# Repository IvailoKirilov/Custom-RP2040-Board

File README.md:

# Custom-RP2040-Board
This board is a simple RP2040 based MCU. The PCB was made with the help of the guide from Hack Club Stasis. 

I decided to make this board because I had wanted to make my own MCU for a while and when I saw the guide I instantly knew I had to make it. I learned quite a bit while making this project and now I will be bale to use this board for other projects.

This board has taken me about 7-8 hours to fully make. Below I have put some images of the finished board.

Schematic:

PCB (front):

PCB (back):

3D View (top):

3D View (bottom):

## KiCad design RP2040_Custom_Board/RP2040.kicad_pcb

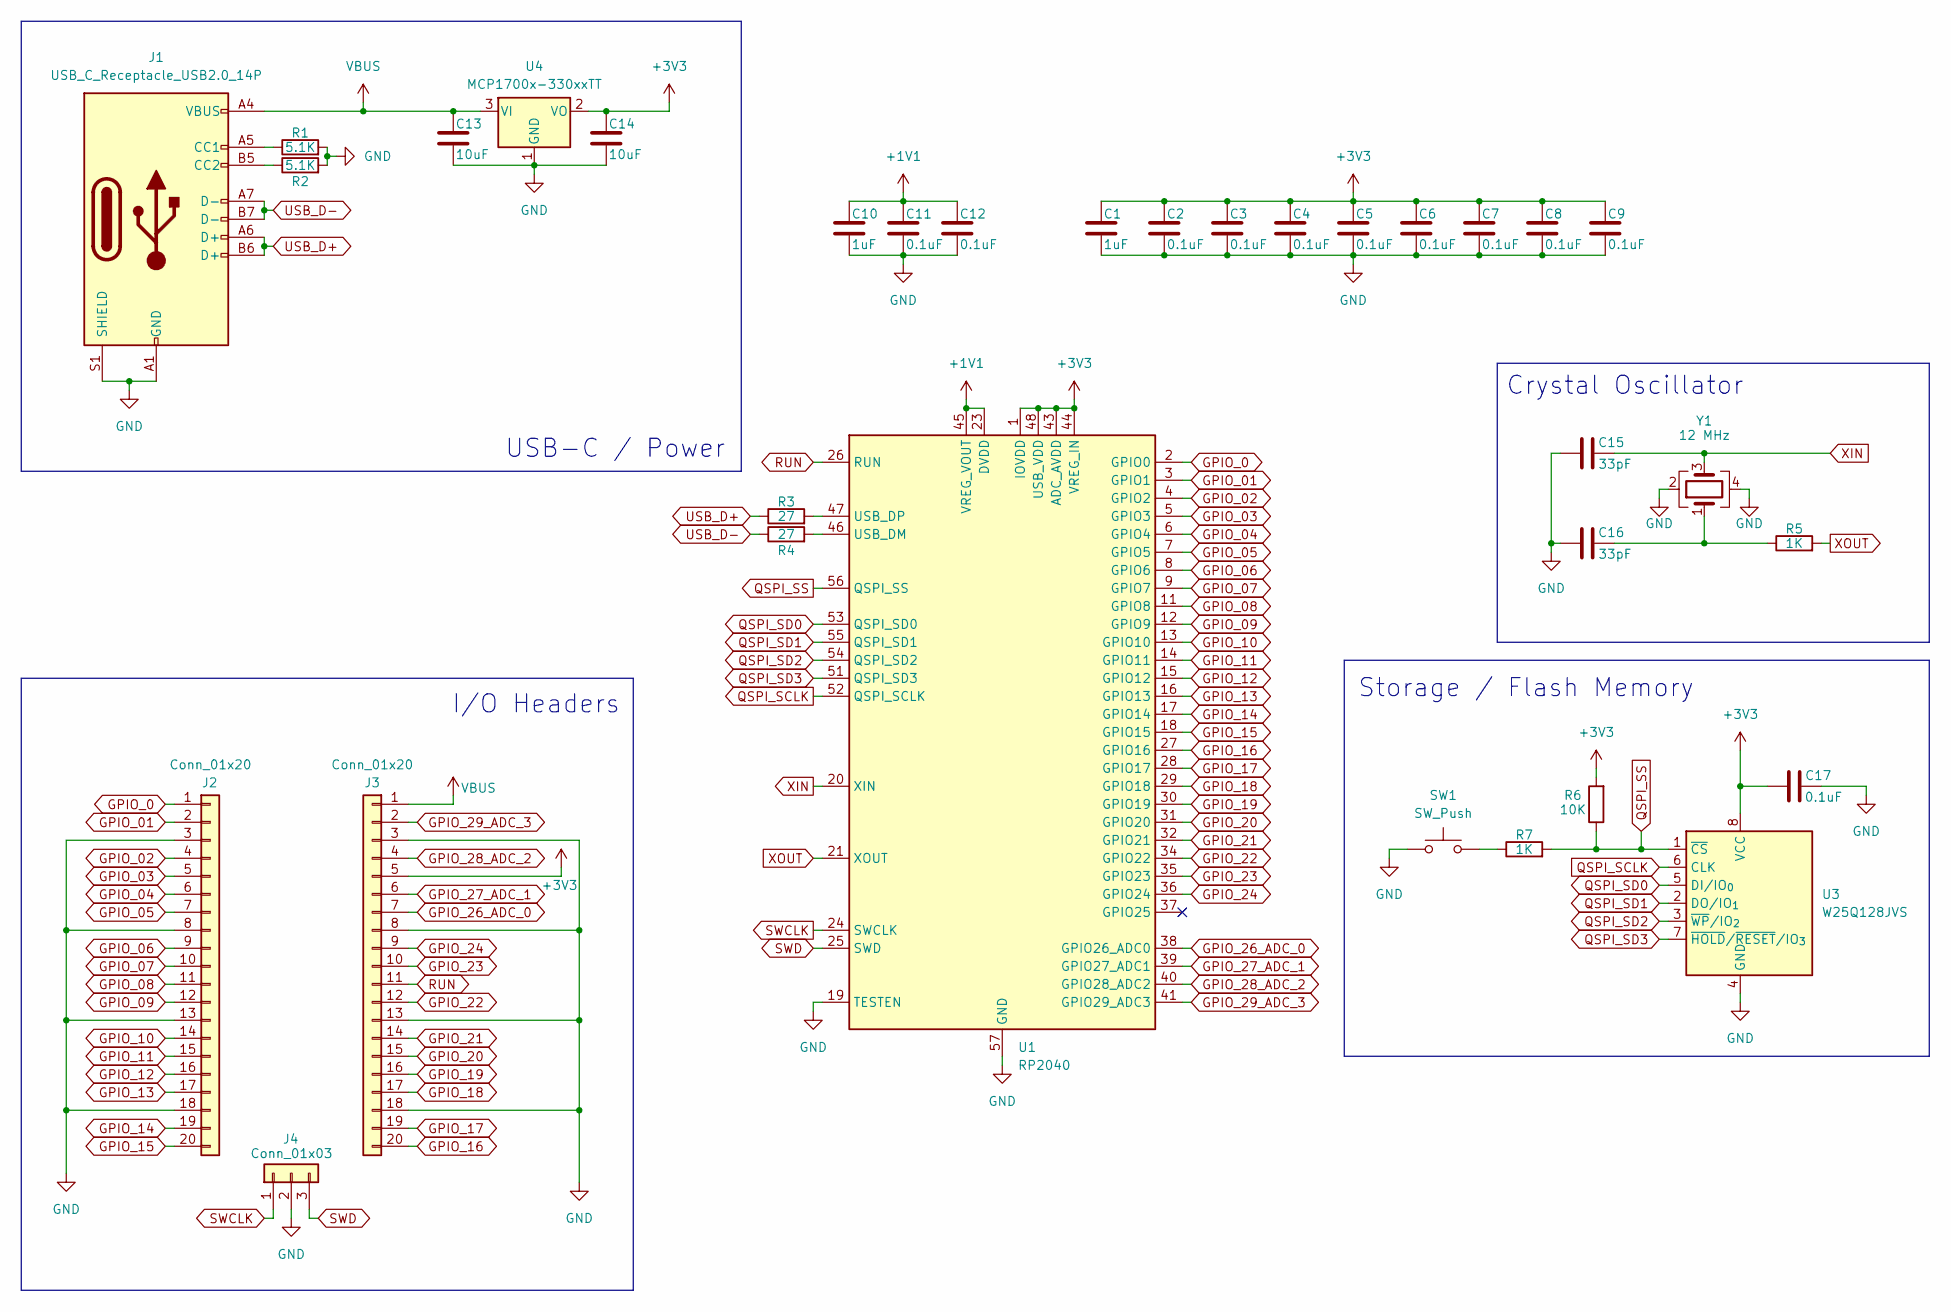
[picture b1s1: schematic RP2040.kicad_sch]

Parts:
C1, C10: 1uF; C_0402_1005Metric
C2, C3, C4, C5, C6, C7, C8, C9, C11, C12, C17: 0.1uF; C_0402_1005Metric
C13, C14: 10uF; C_0603_1608Metric
C15, C16: 33pF; C_0603_1608Metric
J1: USB_C_Receptacle_USB2.0_14P; USB_C_Receptacle_HRO_TYPE-C-31-M-12
J2, J3: Conn_01x20; PinHeader_1x20_P2.54mm_Vertical
J4: Conn_01x03; PinHeader_1x03_P2.54mm_Vertical
R1, R2: 5.1K; R_0402_1005Metric
R3, R4: 27; R_0402_1005Metric
R5, R7: 1K; R_0402_1005Metric
R6: 10K; R_0402_1005Metric
SW1: SW_Push; SW_Push_SPST_NO_Alps_SKRK
U1: RP2040; QFN-56-1EP_7x7mm_P0.4mm_EP3.2x3.2mm
U3: W25Q128JVS; Winbond_USON-8-1EP_3x2mm_P0.5mm_EP0.2x1.6mm
U4: MCP1700x-330xxTT; SOT-23
Y1: 12 MHz; Crystal_SMD_3225-4Pin_3.2x2.5mm

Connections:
+1V1: C10.1, C11.1, C12.1, U1.23 (DVDD), U1.45 (VREG_VOUT), U1.50 (DVDD)
+3V3: C1.1, C2.1, C3.1, C4.1, C5.1, C6.1, C7.1, C8.1, C9.1, C14.1, C17.1, J3.5, R6.2, U1.1 (IOVDD), U1.10 (IOVDD), U1.22 (IOVDD), U1.33 (IOVDD), U1.42 (IOVDD), U1.43 (ADC_AVDD), U1.44 (VREG_IN), U1.48 (USB_VDD), U1.49 (IOVDD), U3.8 (VCC), U4.2 (VO)
GND: C1.2, C2.2, C3.2, C4.2, C5.2, C6.2, C7.2, C8.2, C9.2, C10.2, C11.2, C12.2, C13.2, C14.2, C15.1, C16.1, C17.2, J1.A1 (GND), J1.A12 (GND), J1.B1 (GND), J1.B12 (GND), J1.S1 (SHIELD), J2.3, J2.8, J2.13, J2.18, J3.3, J3.8, J3.13, J3.18, J4.2, R1.2, R2.2, SW1.1, U1.19 (TESTEN), U1.57 (GND), U3.4 (GND), U4.1 (GND), Y1.2, Y1.4
GPIO_0: J2.1, U1.2 (GPIO0)
GPIO_01: J2.2, U1.3 (GPIO1)
GPIO_02: J2.4, U1.4 (GPIO2)
GPIO_03: J2.5, U1.5 (GPIO3)
GPIO_04: J2.6, U1.6 (GPIO4)
GPIO_05: J2.7, U1.7 (GPIO5)
GPIO_06: J2.9, U1.8 (GPIO6)
GPIO_07: J2.10, U1.9 (GPIO7)
GPIO_08: J2.11, U1.11 (GPIO8)
GPIO_09: J2.12, U1.12 (GPIO9)
GPIO_10: J2.14, U1.13 (GPIO10)
GPIO_11: J2.15, U1.14 (GPIO11)
GPIO_12: J2.16, U1.15 (GPIO12)
GPIO_13: J2.17, U1.16 (GPIO13)
GPIO_14: J2.19, U1.17 (GPIO14)
GPIO_15: J2.20, U1.18 (GPIO15)
GPIO_16: J3.20, U1.27 (GPIO16)
GPIO_17: J3.19, U1.28 (GPIO17)
GPIO_18: J3.17, U1.29 (GPIO18)
GPIO_19: J3.16, U1.30 (GPIO19)
GPIO_20: J3.15, U1.31 (GPIO20)
GPIO_21: J3.14, U1.32 (GPIO21)
GPIO_22: J3.12, U1.34 (GPIO22)
GPIO_23: J3.10, U1.35 (GPIO23)
GPIO_24: J3.9, U1.36 (GPIO24)
GPIO_26_ADC_0: J3.7, U1.38 (GPIO26_ADC0)
GPIO_27_ADC_1: J3.6, U1.39 (GPIO27_ADC1)
GPIO_28_ADC_2: J3.4, U1.40 (GPIO28_ADC2)
GPIO_29_ADC_3: J3.2, U1.41 (GPIO29_ADC3)
unnamed: C16.2, R5.1, Y1.1
unnamed: J1.A5 (CC1), R1.1
unnamed: J1.B5 (CC2), R2.1
unnamed: R7.1, SW1.2
unnamed: R4.2, U1.46 (USB_DM)
unnamed: R3.2, U1.47 (USB_DP)
QSPI_SCLK: U1.52 (QSPI_SCLK), U3.6 (CLK)
QSPI_SD0: U1.53 (QSPI_SD0), U3.5 (DI/IO_{0})
QSPI_SD1: U1.55 (QSPI_SD1), U3.2 (DO/IO_{1})
QSPI_SD2: U1.54 (QSPI_SD2), U3.3 (~WP/IO_{2})
QSPI_SD3: U1.51 (QSPI_SD3), U3.7 (~HOLD/~RESET/IO_{3})
QSPI_SS: R6.1, R7.2, U1.56 (QSPI_SS), U3.1 (~CS)
RUN: J3.11, U1.26 (RUN)
SWCLK: J4.1, U1.24 (SWCLK)
SWD: J4.3, U1.25 (SWD)
USB_D+: J1.A6 (D+), J1.B6 (D+), R3.1
USB_D-: J1.A7 (D-), J1.B7 (D-), R4.1
VBUS: C13.1, J1.A4 (VBUS), J1.A9 (VBUS), J1.B4 (VBUS), J1.B9 (VBUS), J3.1, U4.3 (VI)
XIN: C15.2, U1.20 (XIN), Y1.3
XOUT: R5.2, U1.21 (XOUT)

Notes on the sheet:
Storage / Flash Memory
I/O Headers
Crystal Oscillator
USB-C / Power

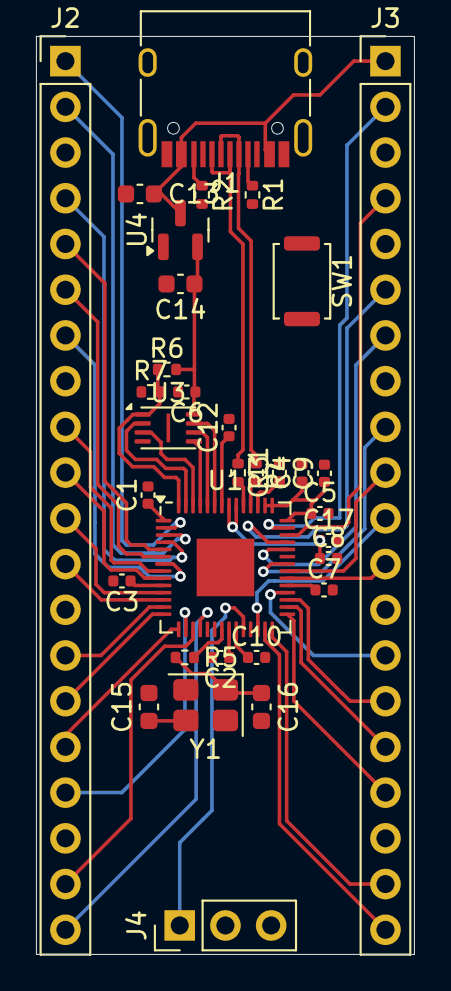
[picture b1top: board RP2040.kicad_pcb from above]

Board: 2 copper layers, 21.0 x 51.0 mm, 33 parts (0 on the bottom side), 52 nets.

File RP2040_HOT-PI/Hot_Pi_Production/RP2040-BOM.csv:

Id;Designator;Footprint;Quantity;Comment;Supplier and ref
1;R5,R7;R_0402_1005Metric;2;1K;
2;SW1;SW_Push_SPST_NO_Alps_SKRK;1;SW_Push;
3;C17,C9,C3,C2,C7,C6,C8,C11,C12,C4,C5;C_0402_1005Metric;11;0.1uF;
4;R3,R4;R_0402_1005Metric;2;27;
5;R6;R_0402_1005Metric;1;10K;
6;C16,C15;C_0603_1608Metric;2;33pF;
7;U3;Winbond_USON-8-1EP_3x2mm_P0.5mm_EP0.2x1.6mm;1;W25Q128JVS;
8;C1,C10;C_0402_1005Metric;2;1uF;
9;R1,R2;R_0402_1005Metric;2;5.1K;
10;J2,J3;PinHeader_1x20_P2.54mm_Vertical;2;Conn_01x20;
11;C13,C14;C_0603_1608Metric;2;10uF;
12;J4;PinHeader_1x03_P2.54mm_Vertical;1;Conn_01x03;
13;Y1;Crystal_SMD_3225-4Pin_3.2x2.5mm;1;12 MHz;
14;U1;QFN-56-1EP_7x7mm_P0.4mm_EP3.2x3.2mm;1;RP2040;
15;U4;SOT-23;1;MCP1700x-330xxTT;
16;J1;USB_C_Receptacle_HRO_TYPE-C-31-M-12;1;USB_C_Receptacle_USB2.0_14P;

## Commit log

2026-03-12 Added the projects files
    Made the schematic.
    Started the PCB.
2026-03-14 Remade the traces on the PCB
2026-03-15 Added custom silkscreen
2026-03-17 Generated files for production
2026-03-17 Updated the README.md
2026-03-17 Fixed README visual bugs
